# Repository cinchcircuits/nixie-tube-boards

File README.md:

nixie-tube-boards
=================

Eagle board files for open source nixie tube boards.

Created by: mgregg@cinchcircuits.com

These boards are distribuited under the TAPR OSH licence 1.0. Commercial use is acceptable.
http://www.tapr.org/ohl.html

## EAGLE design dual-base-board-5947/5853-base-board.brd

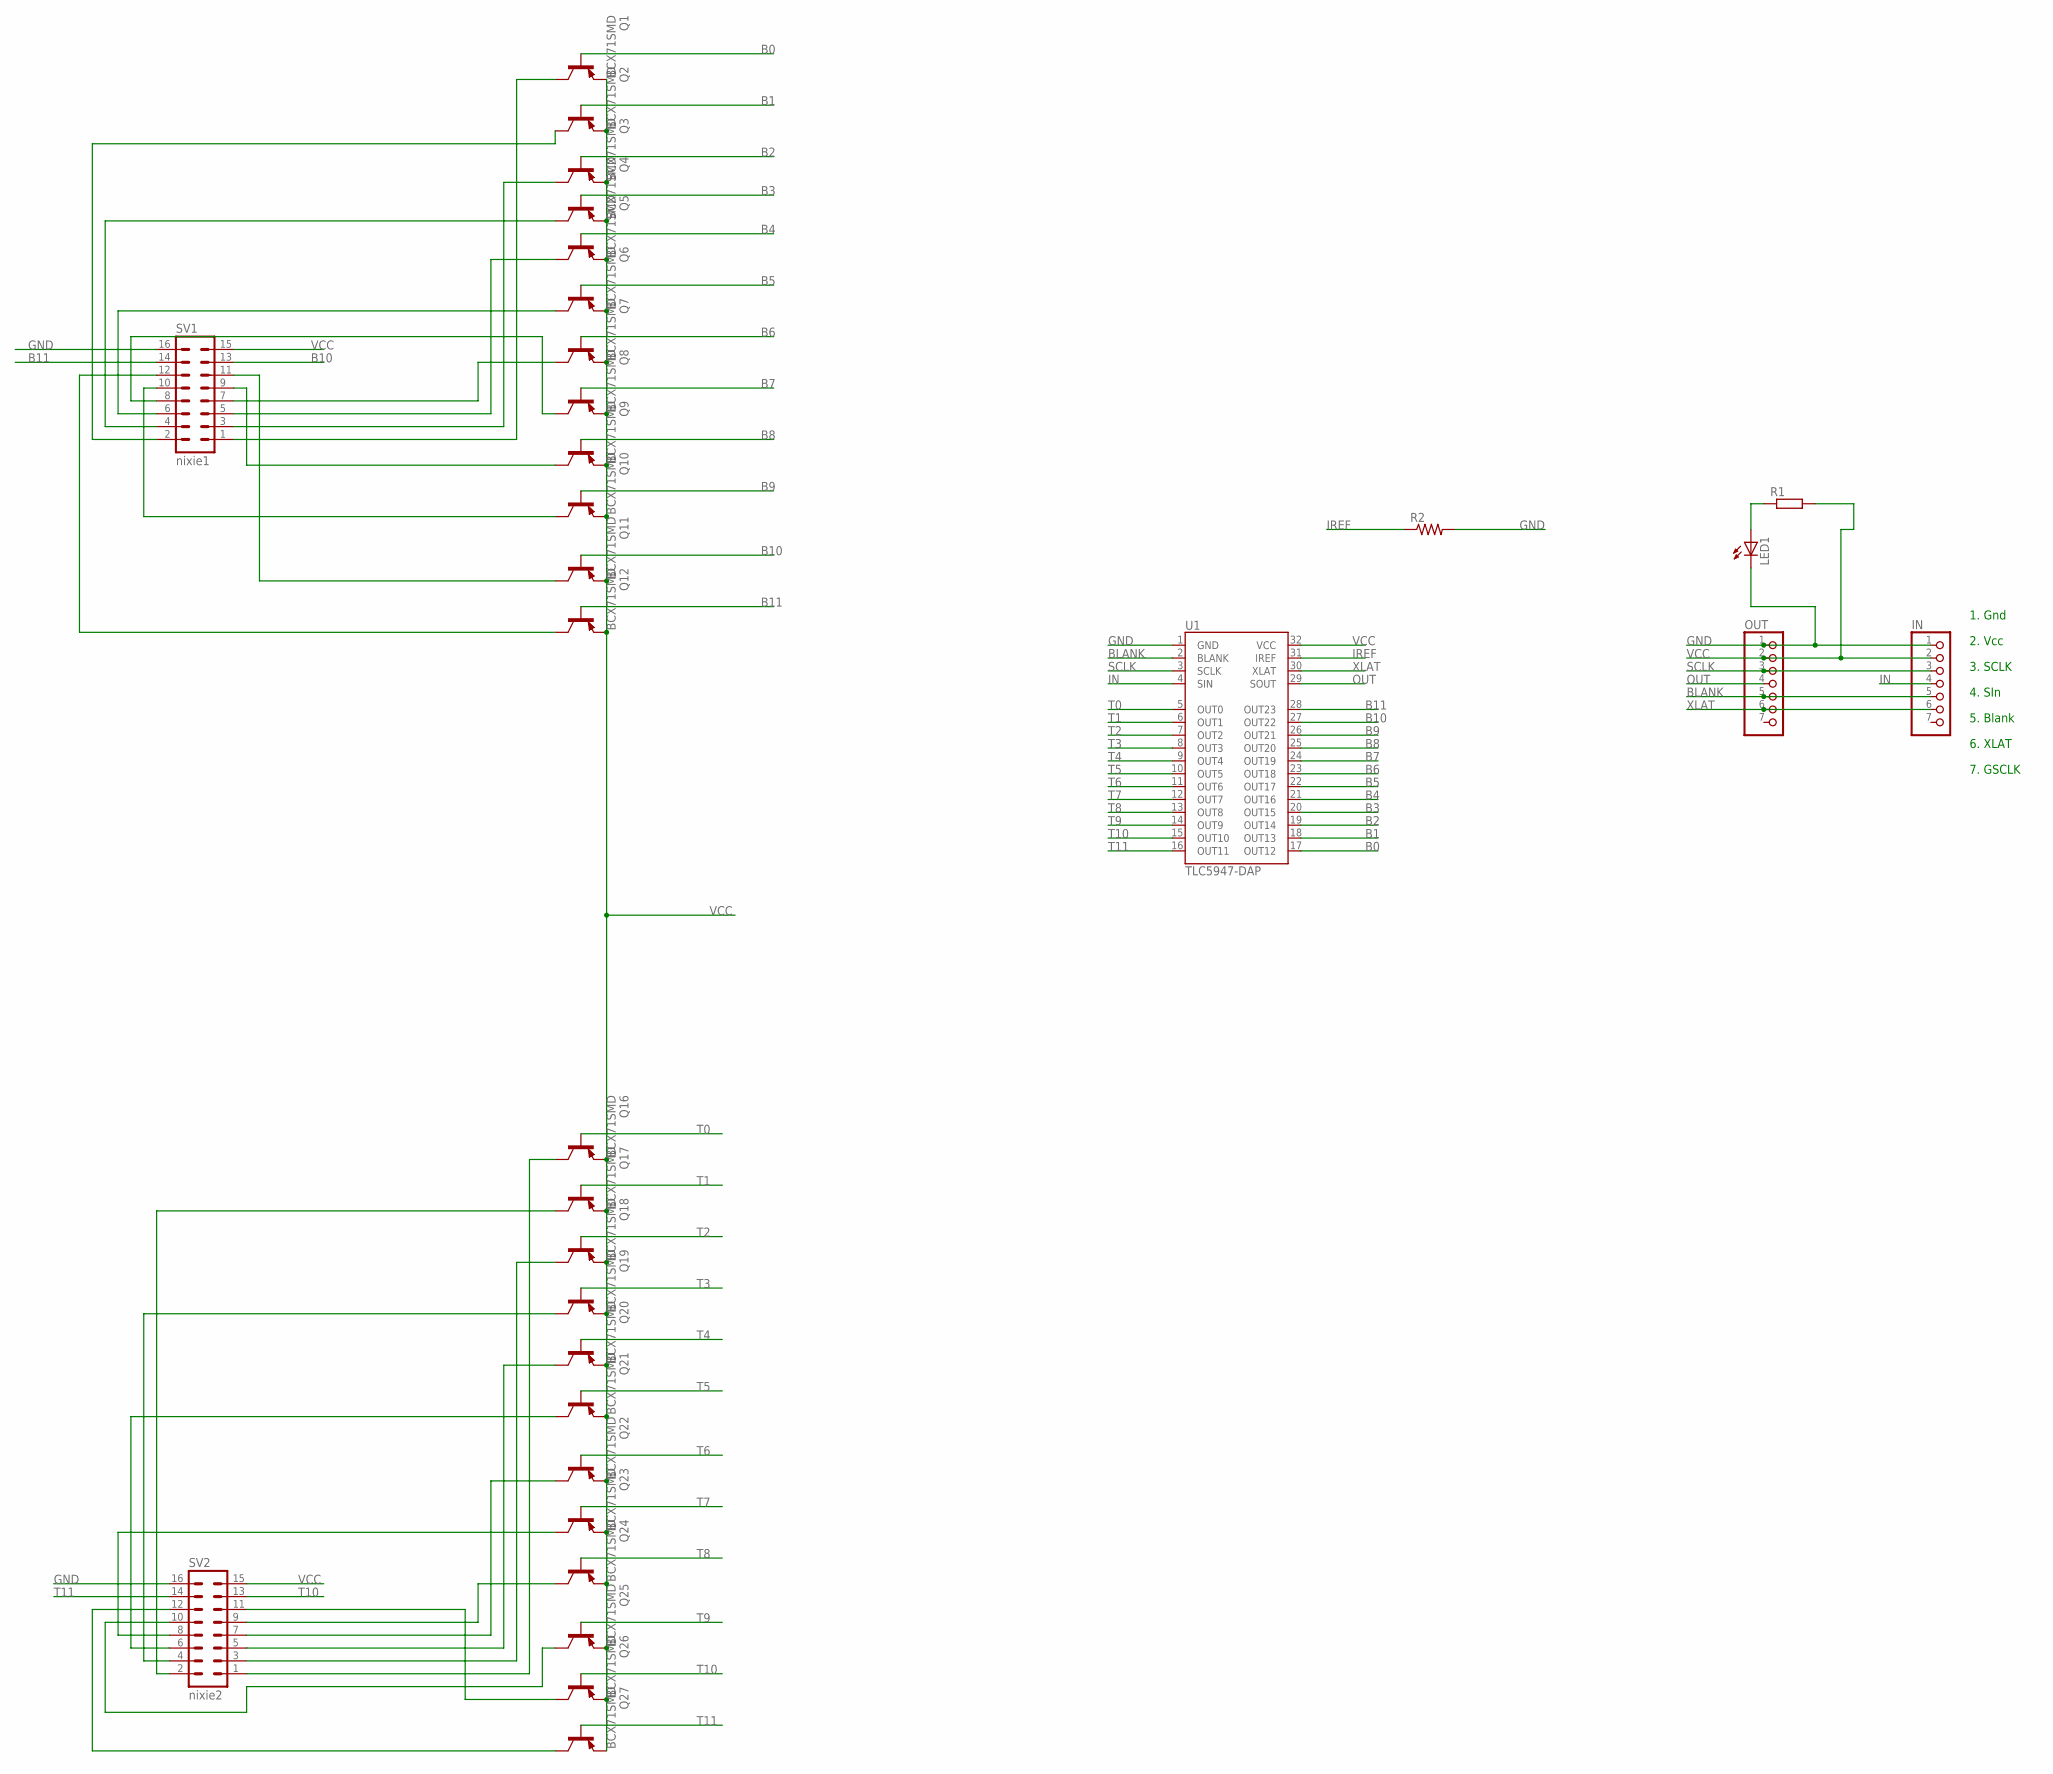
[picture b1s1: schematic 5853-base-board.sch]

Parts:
IN: PINHD-1X7; 1X07
LED1: LEDCHIPLED_0603; CHIPLED_0603
OUT: PINHD-1X7; 1X07
Q1, Q2, Q3, Q4, Q5, Q6, Q7, Q8, Q9, Q10, Q11, Q12, Q16, Q17, Q18, Q19, Q20, Q21, Q22, Q23, Q24, Q25, Q26, Q27: BCX71SMD; SOT23
R1: R-EU_M0805; M0805
R2: R-US_R0805W; R0805W
SV1: nixie1; ML16
SV2: nixie2; ML16
U1: TLC5947-DAP; TSSOP32-GROUNDPAD

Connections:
B0: Q1.1 (B), U1.17 (OUT12)
B1: Q2.1 (B), U1.18 (OUT13)
B2: Q3.1 (B), U1.19 (OUT14)
B3: Q4.1 (B), U1.20 (OUT15)
B4: Q5.1 (B), U1.21 (OUT16)
B5: Q6.1 (B), U1.22 (OUT17)
B6: Q7.1 (B), U1.23 (OUT18)
B7: Q8.1 (B), U1.24 (OUT19)
B8: Q9.1 (B), U1.25 (OUT20)
B9: Q10.1 (B), U1.26 (OUT21)
B10: Q11.1 (B), SV1.13, U1.27 (OUT22)
B11: Q12.1 (B), SV1.14, U1.28 (OUT23)
BLANK: IN.5, OUT.5, U1.2 (BLANK)
GND: IN.1, LED1.C, OUT.1, R2.2, SV1.16, SV2.16, U1.1 (GND)
IN: IN.4, U1.4 (SIN)
IREF: R2.1, U1.31 (IREF)
unnamed: LED1.A, R1.1
unnamed: Q1.3 (C), SV1.1
unnamed: Q2.3 (C), SV1.2
unnamed: Q3.3 (C), SV1.3
unnamed: Q4.3 (C), SV1.4
unnamed: Q5.3 (C), SV1.5
unnamed: Q6.3 (C), SV1.6
unnamed: Q7.3 (C), SV1.7
unnamed: Q8.3 (C), SV1.8
unnamed: Q9.3 (C), SV1.9
unnamed: Q10.3 (C), SV1.10
unnamed: Q11.3 (C), SV1.11
unnamed: Q12.3 (C), SV1.12
unnamed: Q16.3 (C), SV2.1
unnamed: Q17.3 (C), SV2.2
unnamed: Q18.3 (C), SV2.3
unnamed: Q19.3 (C), SV2.4
unnamed: Q20.3 (C), SV2.5
unnamed: Q21.3 (C), SV2.6
unnamed: Q22.3 (C), SV2.7
unnamed: Q23.3 (C), SV2.8
unnamed: Q24.3 (C), SV2.9
unnamed: Q25.3 (C), SV2.10
unnamed: Q26.3 (C), SV2.11
unnamed: Q27.3 (C), SV2.12
OUT: OUT.4, U1.29 (SOUT)
SCLK: IN.3, OUT.3, U1.3 (SCLK)
T0: Q16.1 (B), U1.5 (OUT0)
T1: Q17.1 (B), U1.6 (OUT1)
T2: Q18.1 (B), U1.7 (OUT2)
T3: Q19.1 (B), U1.8 (OUT3)
T4: Q20.1 (B), U1.9 (OUT4)
T5: Q21.1 (B), U1.10 (OUT5)
T6: Q22.1 (B), U1.11 (OUT6)
T7: Q23.1 (B), U1.12 (OUT7)
T8: Q24.1 (B), U1.13 (OUT8)
T9: Q25.1 (B), U1.14 (OUT9)
T10: Q26.1 (B), SV2.13, U1.15 (OUT10)
T11: Q27.1 (B), SV2.14, U1.16 (OUT11)
VCC: IN.2, OUT.2, Q1.2 (E), Q2.2 (E), Q3.2 (E), Q4.2 (E), Q5.2 (E), Q6.2 (E), Q7.2 (E), Q8.2 (E), Q9.2 (E), Q10.2 (E), Q11.2 (E), Q12.2 (E), Q16.2 (E), Q17.2 (E), Q18.2 (E), Q19.2 (E), Q20.2 (E), Q21.2 (E), Q22.2 (E), Q23.2 (E), Q24.2 (E), Q25.2 (E), Q26.2 (E), Q27.2 (E), R1.2, SV1.15, SV2.15, U1.32 (VCC)
XLAT: IN.6, OUT.6, U1.30 (XLAT)

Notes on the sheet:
1. Gnd
2. Vcc
3. SCLK
4. SIn
5. Blank
6. XLAT
7. GSCLK

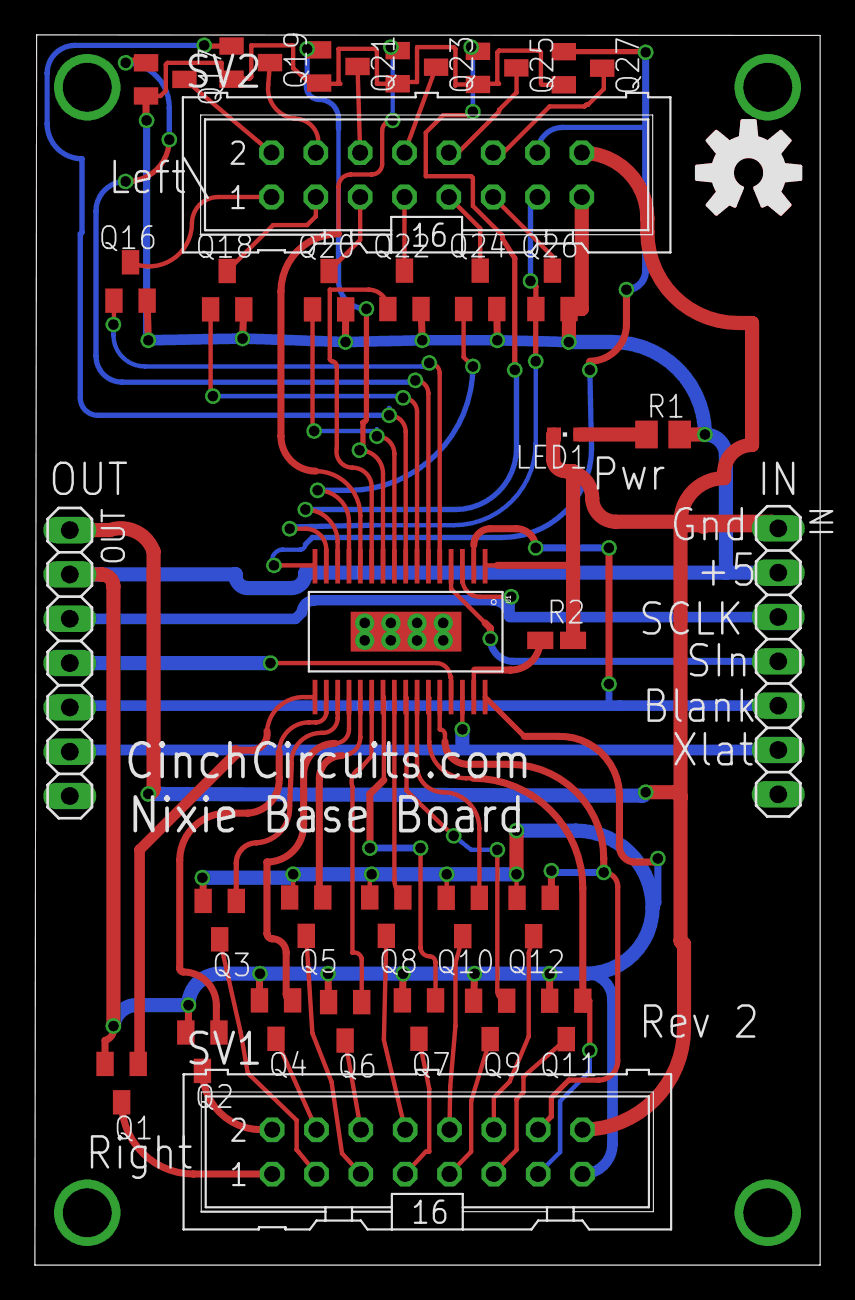
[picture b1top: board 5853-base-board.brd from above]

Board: 2 copper layers, 45.0 x 70.5 mm, 32 parts (0 on the bottom side), 57 nets.

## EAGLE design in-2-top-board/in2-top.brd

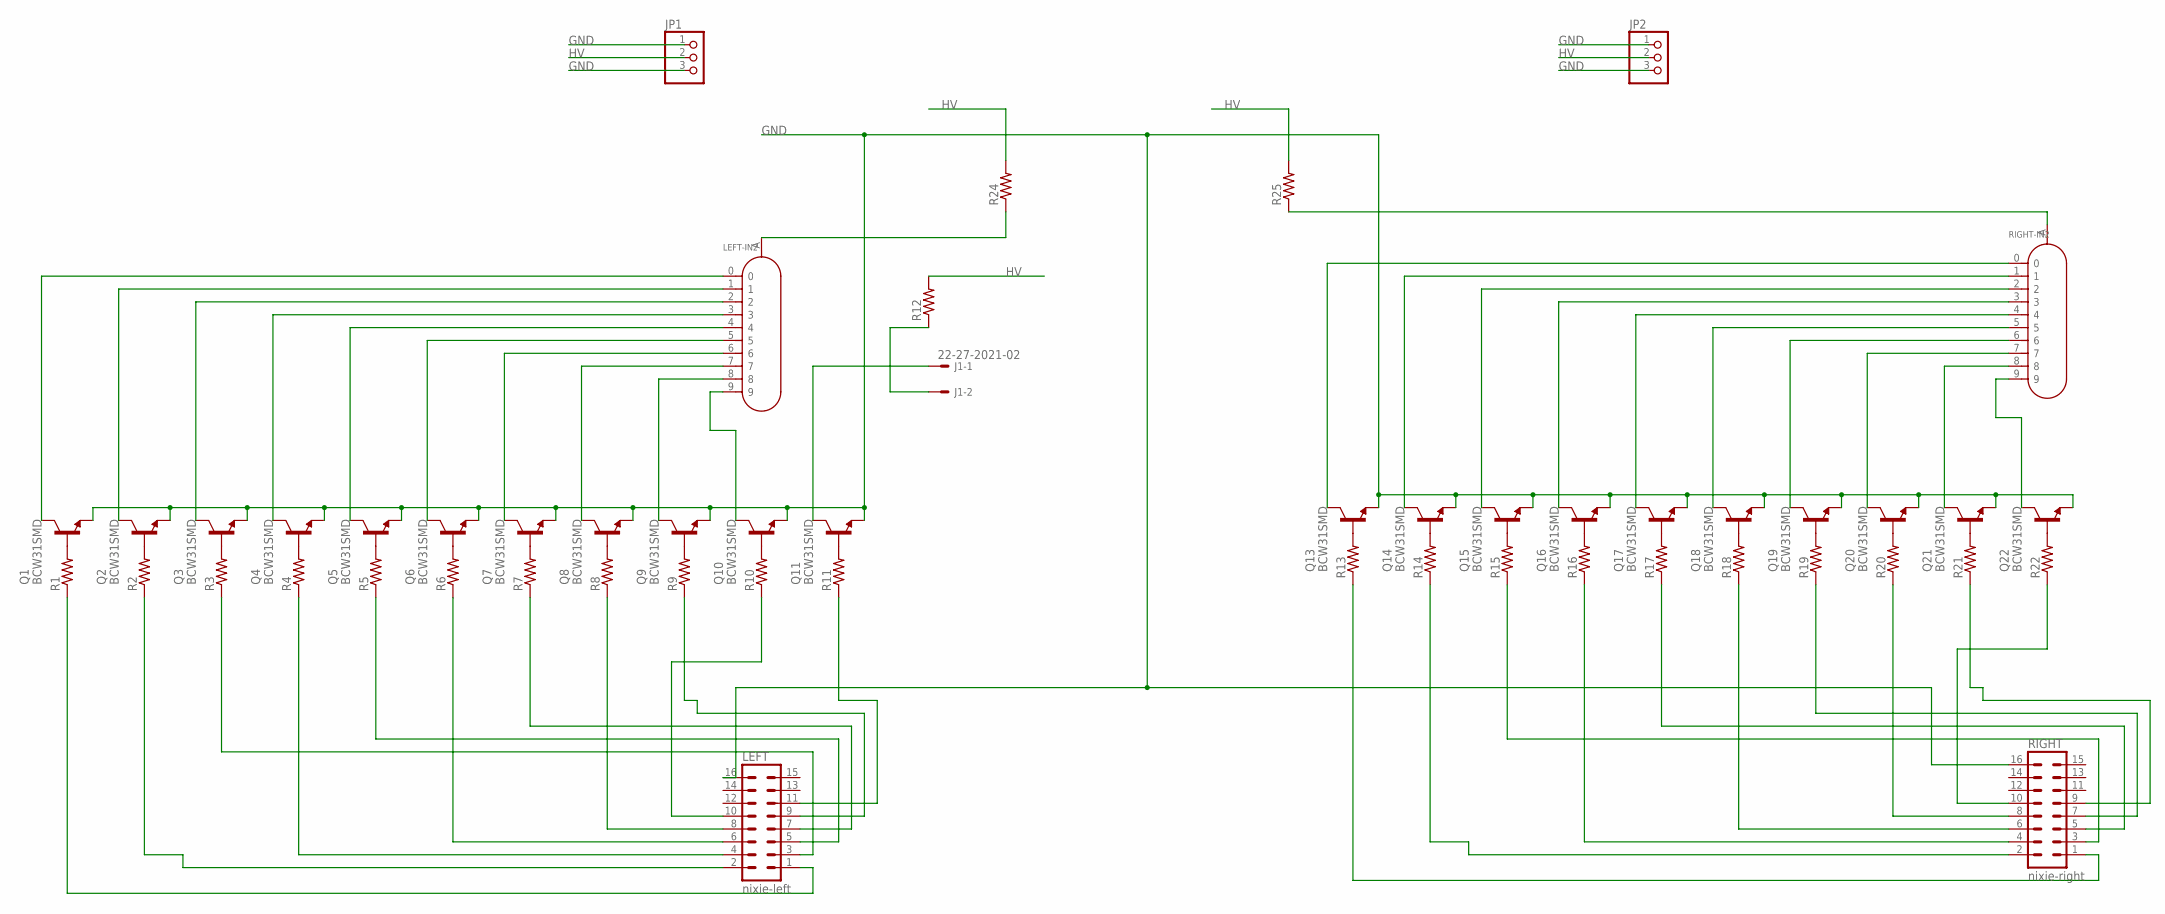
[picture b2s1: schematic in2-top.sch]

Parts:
J1: 22-27-2021-02; 6410-02
JP1, JP2: PINHD-1X3; 1X03
LEFT: nixie-left; ML16
LEFT-IN2: IN-2
Q1, Q2, Q3, Q4, Q5, Q6, Q7, Q8, Q9, Q10, Q11, Q13, Q14, Q15, Q16, Q17, Q18, Q19, Q20, Q21, Q22: BCW31SMD; SOT23-BEC
R1, R2, R3, R4, R5, R6, R7, R8, R9, R10, R11, R13, R14, R15, R16, R17, R18, R19, R20, R21, R22: R-US_M0805; M0805
R12, R24, R25: R-US_R0805; R0805
RIGHT: nixie-right; ML16
RIGHT-IN2: IN-2

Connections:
GND: JP1.1, JP1.3, JP2.1, JP2.3, LEFT.16, Q1.E, Q2.E, Q3.E, Q4.E, Q5.E, Q6.E, Q7.E, Q8.E, Q9.E, Q10.E, Q11.E, Q13.E, Q14.E, Q15.E, Q16.E, Q17.E, Q18.E, Q19.E, Q20.E, Q21.E, Q22.E, RIGHT.16
HV: JP1.2, JP2.2, R12.2, R24.2, R25.2
unnamed: LEFT-IN2.0, Q1.C
unnamed: LEFT-IN2.1, Q2.C
unnamed: Q1.B, R1.2
unnamed: Q2.B, R2.2
unnamed: Q3.B, R3.2
unnamed: Q4.B, R4.2
unnamed: Q5.B, R5.2
unnamed: Q6.B, R6.2
unnamed: Q7.B, R7.2
unnamed: Q8.B, R8.2
unnamed: Q9.B, R9.2
unnamed: Q10.B, R10.2
unnamed: Q11.B, R11.2
unnamed: LEFT-IN2.A, R24.1
unnamed: LEFT-IN2.2, Q3.C
unnamed: LEFT-IN2.3, Q4.C
unnamed: LEFT-IN2.4, Q5.C
unnamed: LEFT-IN2.5, Q6.C
unnamed: LEFT-IN2.6, Q7.C
unnamed: LEFT-IN2.7, Q8.C
unnamed: LEFT-IN2.8, Q9.C
unnamed: LEFT-IN2.9, Q10.C
unnamed: Q13.B, R13.2
unnamed: Q14.B, R14.2
unnamed: LEFT.1, R1.1
unnamed: LEFT.2, R2.1
unnamed: LEFT.3, R3.1
unnamed: LEFT.4, R4.1
unnamed: LEFT.5, R5.1
unnamed: LEFT.6, R6.1
unnamed: LEFT.7, R7.1
unnamed: LEFT.8, R8.1
unnamed: LEFT.9, R9.1
unnamed: LEFT.10, R10.1
unnamed: LEFT.11, R11.1
unnamed: R25.1, RIGHT-IN2.A
unnamed: Q15.B, R15.2
unnamed: Q16.B, R16.2
unnamed: Q17.B, R17.2
unnamed: Q18.B, R18.2
unnamed: Q19.B, R19.2
unnamed: Q20.B, R20.2
unnamed: Q21.B, R21.2
unnamed: Q22.B, R22.2
unnamed: R13.1, RIGHT.1
unnamed: R14.1, RIGHT.2
unnamed: R15.1, RIGHT.3
unnamed: R16.1, RIGHT.4
unnamed: R17.1, RIGHT.5
unnamed: R18.1, RIGHT.6
unnamed: R19.1, RIGHT.7
unnamed: R20.1, RIGHT.8
unnamed: R21.1, RIGHT.9
unnamed: R22.1, RIGHT.10
unnamed: J1.2, R12.1
unnamed: Q13.C, RIGHT-IN2.0
unnamed: Q14.C, RIGHT-IN2.1
unnamed: Q15.C, RIGHT-IN2.2
unnamed: Q16.C, RIGHT-IN2.3
unnamed: Q17.C, RIGHT-IN2.4
unnamed: Q18.C, RIGHT-IN2.5
unnamed: Q19.C, RIGHT-IN2.6
unnamed: Q20.C, RIGHT-IN2.7
unnamed: Q21.C, RIGHT-IN2.8
unnamed: Q22.C, RIGHT-IN2.9
unnamed: J1.1, Q11.C

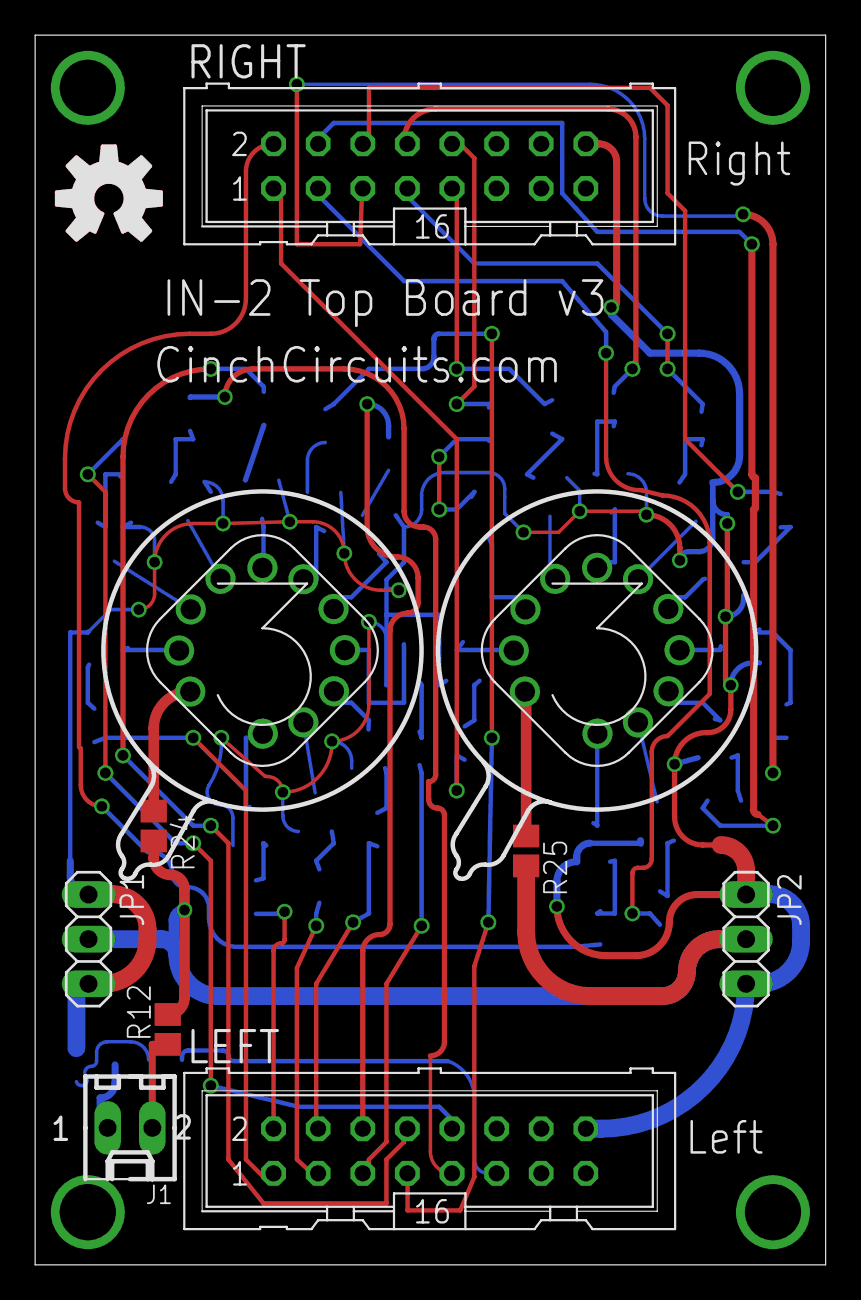
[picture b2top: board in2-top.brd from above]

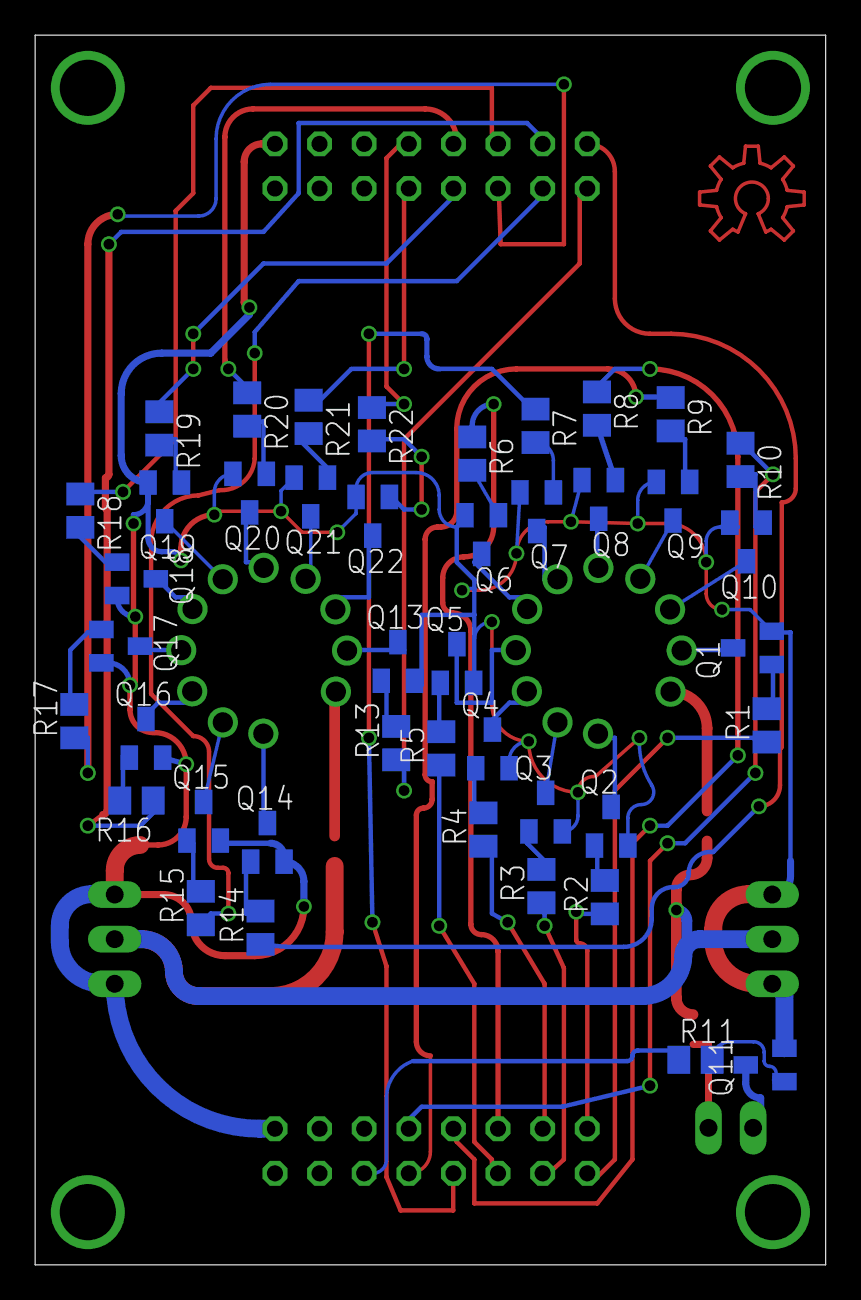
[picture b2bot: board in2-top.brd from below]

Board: 2 copper layers, 45.0 x 70.0 mm, 52 parts (42 on the bottom side), 68 nets.

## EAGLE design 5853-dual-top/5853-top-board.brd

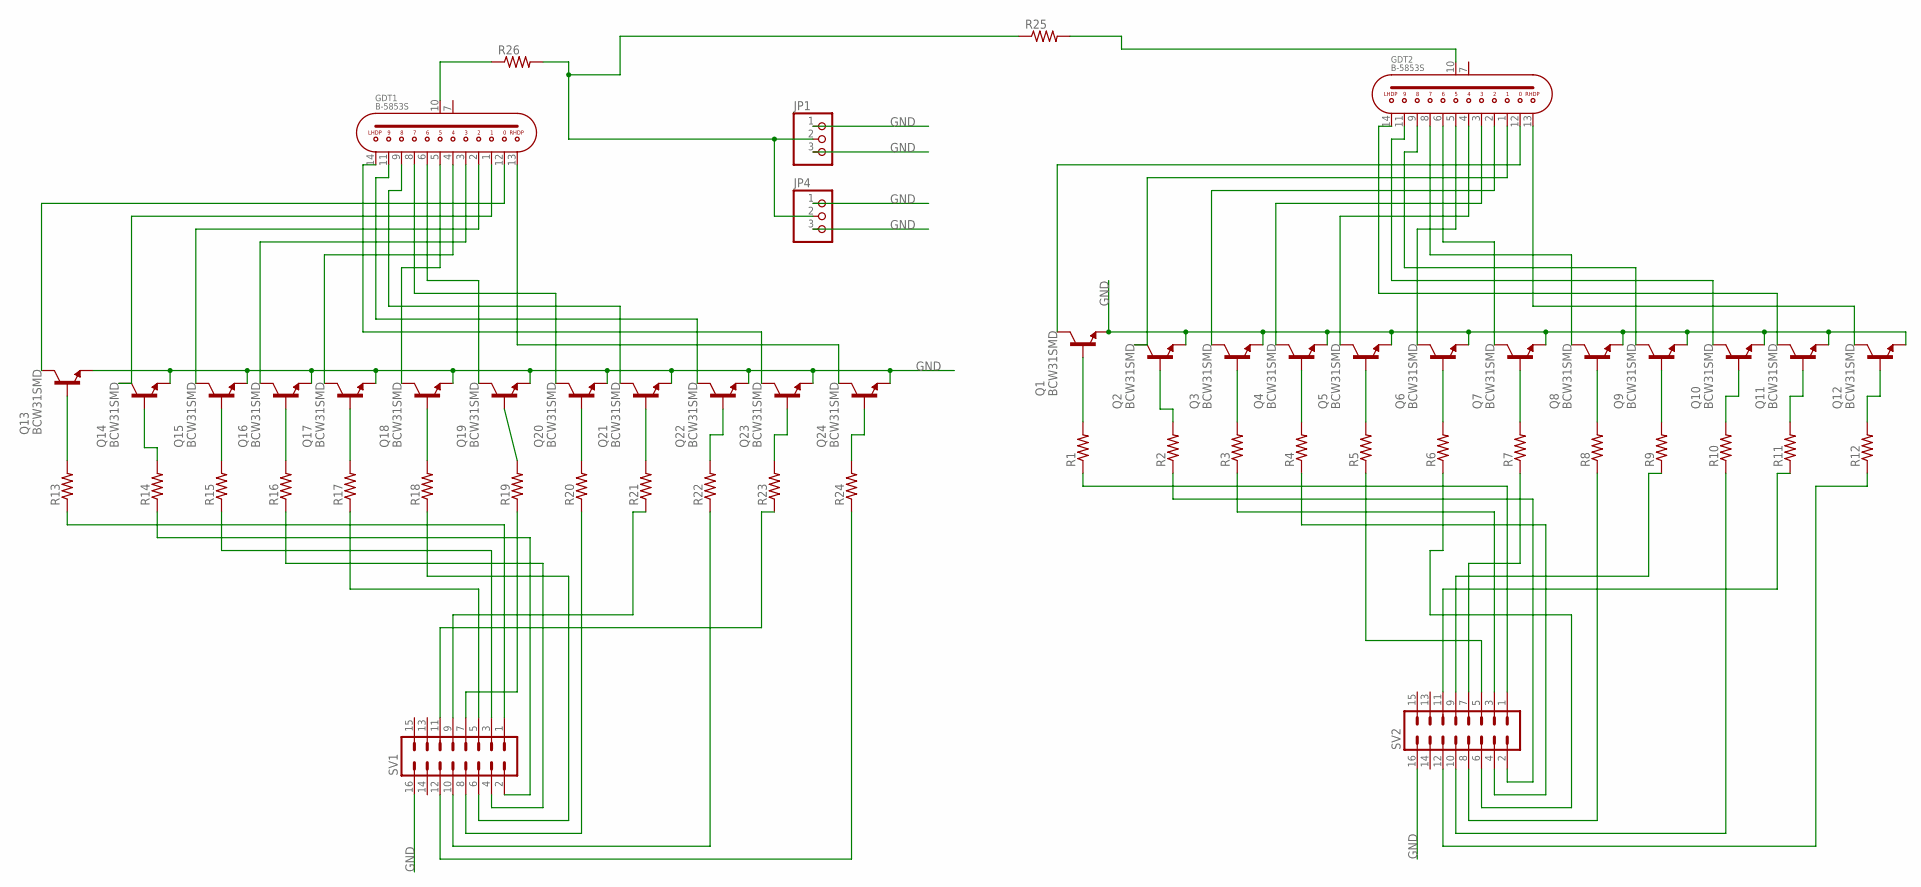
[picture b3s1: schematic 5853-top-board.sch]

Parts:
GDT1, GDT2: B-5853S; SK-207
JP1, JP4: PINHD-1X3; 1X03
Q1, Q2, Q3, Q4, Q5, Q6, Q7, Q8, Q9, Q10, Q11, Q12, Q13, Q14, Q15, Q16, Q17, Q18, Q19, Q20, Q21, Q22, Q23, Q24: BCW31SMD; SOT23-BEC
R1, R2, R3, R4, R5, R6, R7, R8, R9, R10, R11, R12, R13, R14, R15, R16, R17, R18, R19, R20, R21, R22, R23, R24, R25, R26: R-US_M0805; M0805
SV1, SV2: ML16

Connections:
GND: JP1.1, JP1.3, JP4.1, JP4.3, Q1.E, Q2.E, Q3.E, Q4.E, Q5.E, Q6.E, Q7.E, Q8.E, Q9.E, Q10.E, Q11.E, Q12.E, Q13.E, Q14.E, Q15.E, Q16.E, Q17.E, Q18.E, Q19.E, Q20.E, Q21.E, Q22.E, Q23.E, Q24.E, SV1.16, SV2.16
unnamed: R13.1, SV1.1
unnamed: R14.1, SV1.2
unnamed: R15.1, SV1.3
unnamed: R16.1, SV1.4
unnamed: R17.1, SV1.5
unnamed: R18.1, SV1.6
unnamed: R19.1, SV1.7
unnamed: R20.1, SV1.8
unnamed: R21.1, SV1.9
unnamed: R22.1, SV1.10
unnamed: R24.1, SV1.12
unnamed: R23.1, SV1.11
unnamed: JP1.2, JP4.2, R25.1, R26.2
unnamed: GDT1.10, R26.1
unnamed: Q1.B, R1.2
unnamed: GDT1.2, Q15.C
unnamed: GDT1.4, Q17.C
unnamed: GDT1.5, Q18.C
unnamed: GDT1.6, Q19.C
unnamed: GDT1.8, Q20.C
unnamed: GDT1.9, Q21.C
unnamed: GDT1.11, Q22.C
unnamed: GDT1.14, Q23.C
unnamed: GDT1.13, Q24.C
unnamed: Q13.B, R13.2
unnamed: Q14.B, R14.2
unnamed: Q15.B, R15.2
unnamed: Q16.B, R16.2
unnamed: Q17.B, R17.2
unnamed: Q18.B, R18.2
unnamed: Q19.B, R19.2
unnamed: Q20.B, R20.2
unnamed: Q24.B, R24.2
unnamed: Q23.B, R23.2
unnamed: Q22.B, R22.2
unnamed: Q21.B, R21.2
unnamed: GDT1.12, Q13.C
unnamed: Q2.B, R2.2
unnamed: Q3.B, R3.2
unnamed: Q4.B, R4.2
unnamed: Q5.B, R5.2
unnamed: Q6.B, R6.2
unnamed: Q7.B, R7.2
unnamed: Q8.B, R8.2
unnamed: Q12.B, R12.2
unnamed: Q11.B, R11.2
unnamed: Q10.B, R10.2
unnamed: Q9.B, R9.2
unnamed: GDT2.3, Q4.C
unnamed: GDT2.4, Q5.C
unnamed: GDT1.1, Q14.C
unnamed: GDT1.3, Q16.C
unnamed: GDT2.5, Q6.C
unnamed: GDT2.6, Q7.C
unnamed: GDT2.8, Q8.C
unnamed: GDT2.9, Q9.C
unnamed: GDT2.11, Q10.C
unnamed: GDT2.14, Q11.C
unnamed: GDT2.13, Q12.C
unnamed: GDT2.1, Q2.C
unnamed: GDT2.2, Q3.C
unnamed: GDT2.12, Q1.C
unnamed: R2.1, SV2.2
unnamed: R3.1, SV2.3
unnamed: R4.1, SV2.4
unnamed: R5.1, SV2.5
unnamed: R12.1, SV2.12
unnamed: R7.1, SV2.7
unnamed: R8.1, SV2.8
unnamed: R9.1, SV2.9
unnamed: R10.1, SV2.10
unnamed: R11.1, SV2.11
unnamed: R6.1, SV2.6
unnamed: R1.1, SV2.1
unnamed: GDT2.10, R25.2

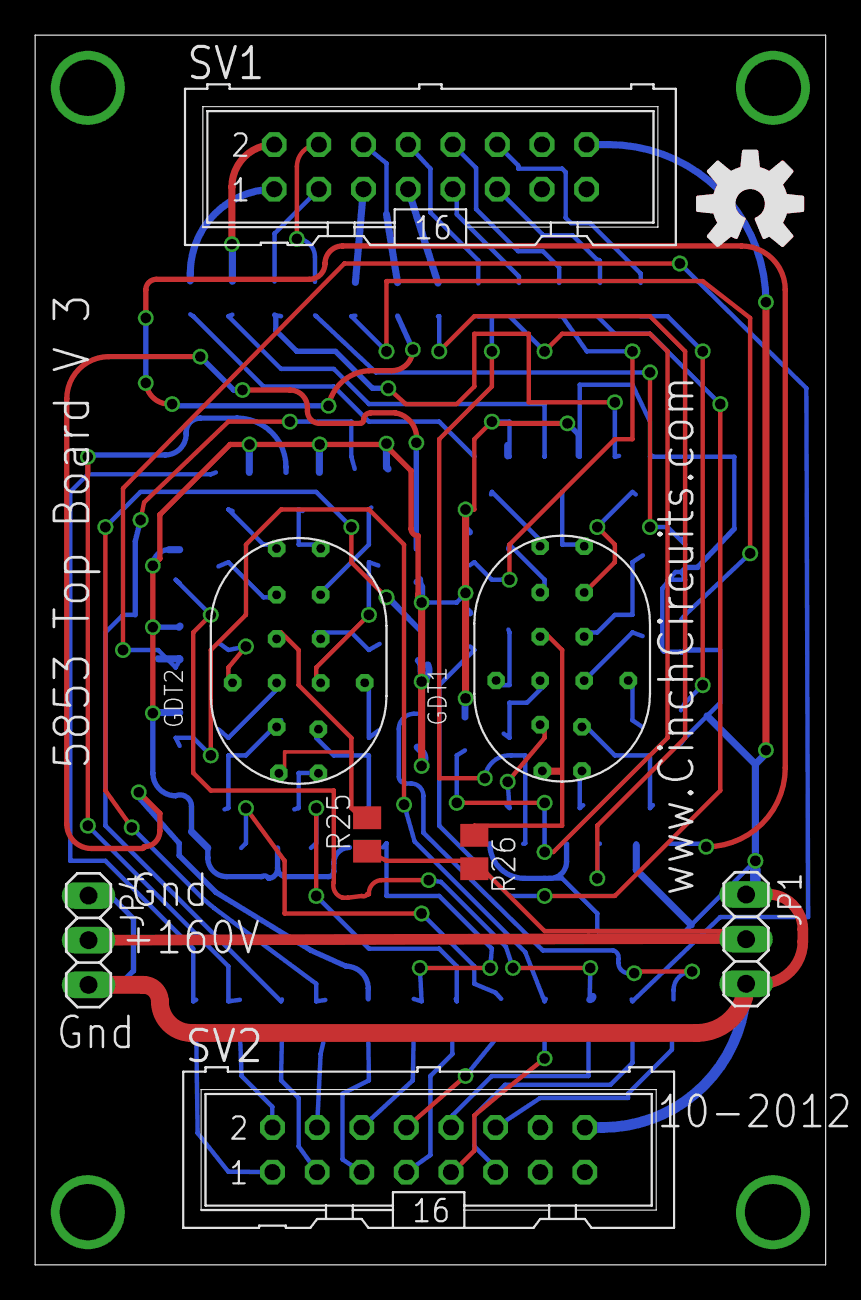
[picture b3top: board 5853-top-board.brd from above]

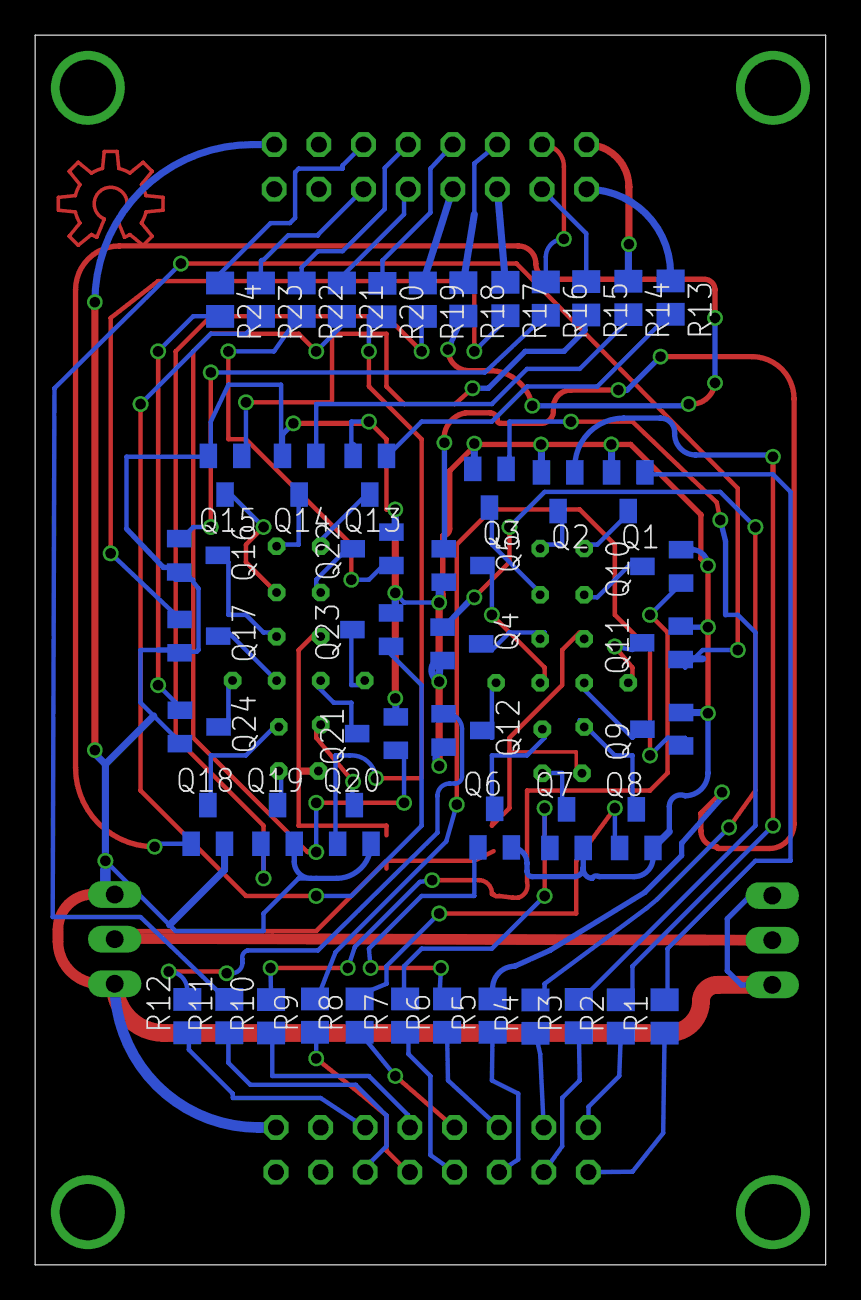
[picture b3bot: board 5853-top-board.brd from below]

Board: 2 copper layers, 45.0 x 70.0 mm, 56 parts (48 on the bottom side), 76 nets.

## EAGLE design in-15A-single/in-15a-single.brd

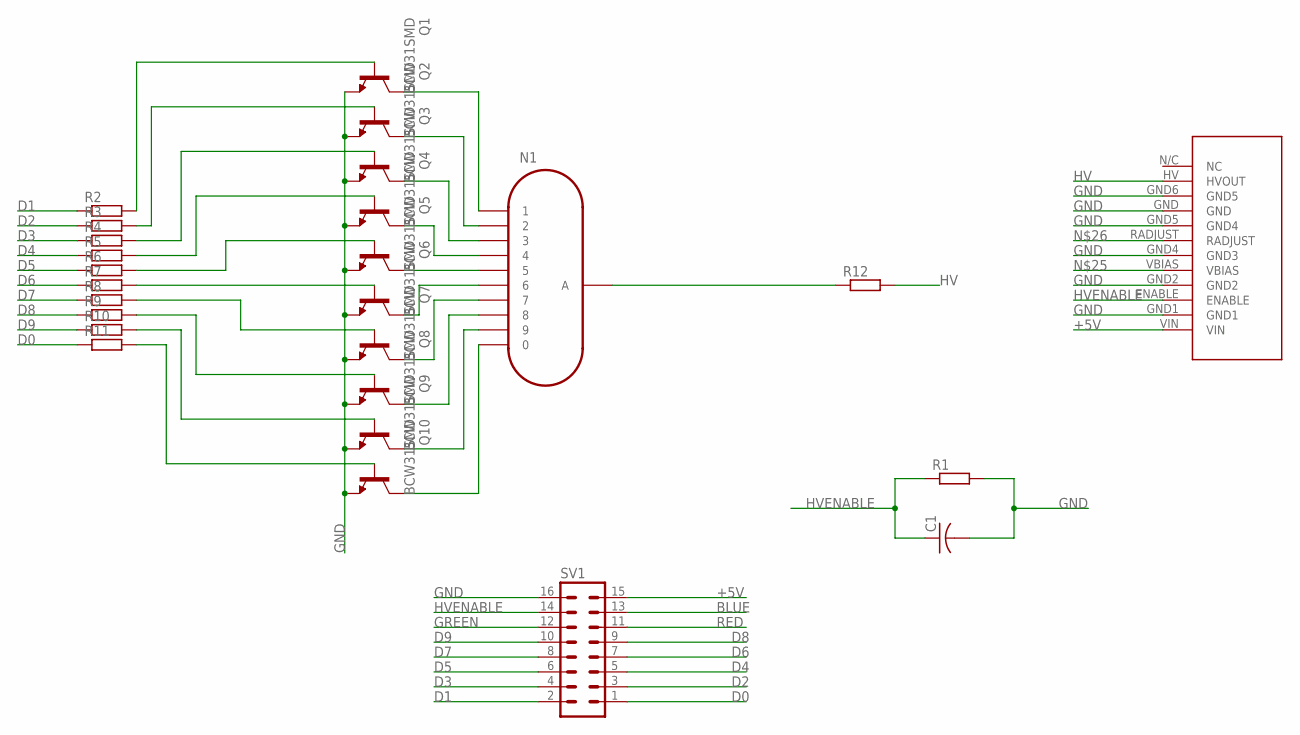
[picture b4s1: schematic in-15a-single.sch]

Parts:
C1: C-USC0805; C0805
N1: IN-12A; IN-12-BIG
Q1, Q2, Q3, Q4, Q5, Q6, Q7, Q8, Q9, Q10: BCW31SMD; SOT23-BEC
R1, R2, R3, R4, R5, R6, R7, R8, R9, R10, R11, R12: R-EU_M0805; M0805
SV1: ML16
U$1: HV-MODULE-EBAY; NIIE-HV

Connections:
+5V: SV1.15, U$1.VIN
BLUE: SV1.13
D0: R11.1, SV1.1
D1: R2.1, SV1.2
D2: R3.1, SV1.3
D3: R4.1, SV1.4
D4: R5.1, SV1.5
D5: R6.1, SV1.6
D6: R7.1, SV1.7
D7: R8.1, SV1.8
D8: R9.1, SV1.9
D9: R10.1, SV1.10
GND: C1.2, Q1.E, Q2.E, Q3.E, Q4.E, Q5.E, Q6.E, Q7.E, Q8.E, Q9.E, Q10.E, R1.2, SV1.16, U$1.GND, U$1.GND1, U$1.GND2, U$1.GND4 (GND3), U$1.GND5 (GND4), U$1.GND6 (GND5)
GREEN: SV1.12
HV: R12.2, U$1.HV (HVOUT)
HVENABLE: C1.1, R1.1, SV1.14, U$1.ENABLE
unnamed: N1.1, Q1.C
unnamed: N1.2, Q2.C
unnamed: N1.3, Q3.C
unnamed: N1.4, Q4.C
unnamed: N1.5, Q5.C
unnamed: N1.6, Q6.C
unnamed: N1.7, Q7.C
unnamed: N1.8, Q8.C
unnamed: N1.9, Q9.C
unnamed: N1.0, Q10.C
unnamed: Q1.B, R2.2
unnamed: Q2.B, R3.2
unnamed: Q3.B, R4.2
unnamed: Q4.B, R5.2
unnamed: Q5.B, R6.2
unnamed: Q6.B, R7.2
unnamed: Q7.B, R8.2
unnamed: Q8.B, R9.2
unnamed: Q9.B, R10.2
unnamed: Q10.B, R11.2
unnamed: N1.A, R12.1
RED: SV1.11

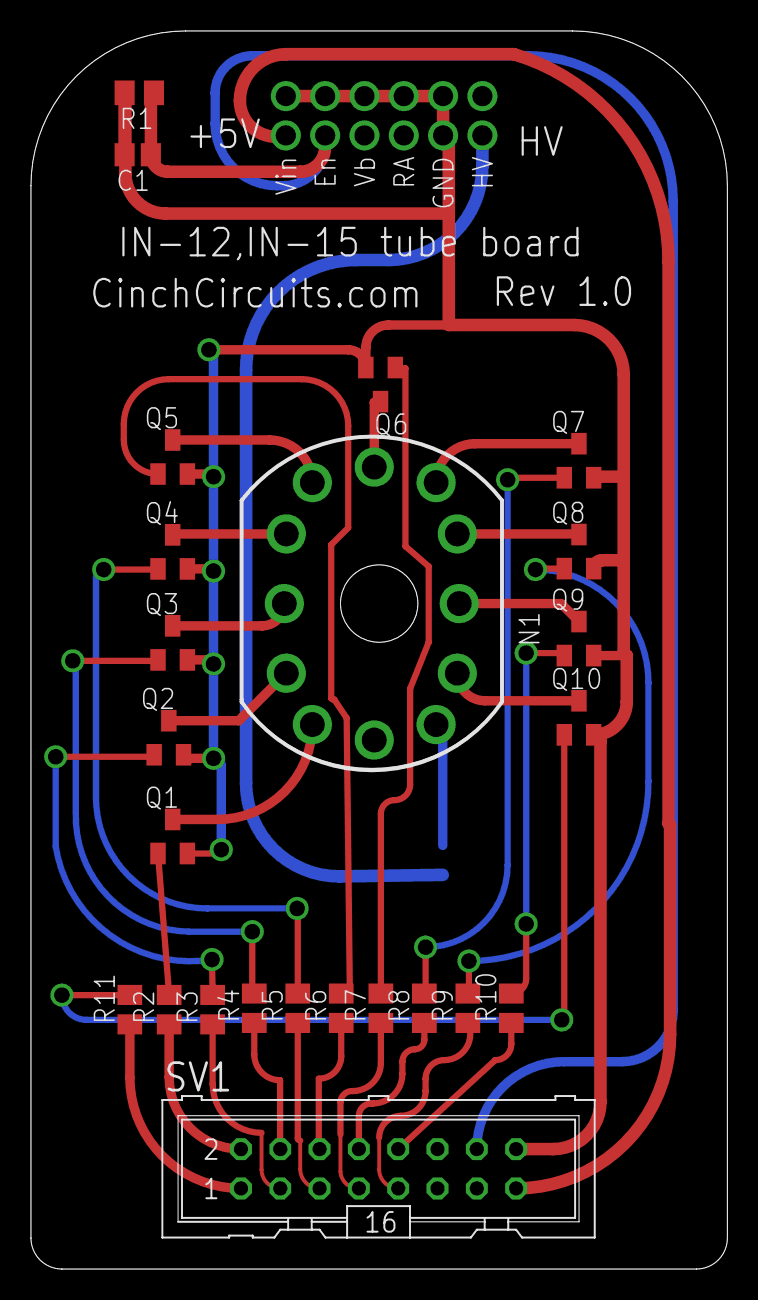
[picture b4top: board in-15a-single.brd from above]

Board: 2 copper layers, 45.0 x 80.0 mm, 27 parts (1 on the bottom side), 35 nets.

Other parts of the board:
U$2: OSHWLOGO_TOL_0.2

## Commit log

2013-05-09 Squashed commit of the following:
    commit e111b6f258c2b02d8c7ad45fe7f01d9900a1ecff
    Author: Michael Gregg <mgregg@redhat.com>
    Date: Thu May 9 13:47:52 2013 -0700
    adding initial nixie tube boards to nixie tube board repo

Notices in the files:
parts and their libraries:
SparkFun: Licensing: CC v3.0 Share-Alike You are welcome to use this library for commercial purposes.
